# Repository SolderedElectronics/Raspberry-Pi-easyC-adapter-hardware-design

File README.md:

# Raspberry Pi easyC adapter Hardware design

## About the product

|  |
| :----------------------------------------------------------: |
|      [Buy Raspberry Pi easyC adapter](https://www.solde.red/333019)      |
This adapter makes it easy to connect easyC devices and sensors to the Raspberry Pi. It has 2 pieces of easyC connectors and a female header for Raspberry Pi, next to the header there are pins for connecting 5V and 3.3V and ground pins. It simply connects to the Raspberry Pi because its pinout matches the pinout of the Raspberry Pi. You can find more about easyC here.

## Repository contents

All Soldered Electronics hardware designed in KiCAD, and repositories are organized in the following way:

- CAD folder - contains KiCAD files (Schematics, Board, Panel Board), sorted by version. Change log lists all changes between versions.
- OUTPUTS - contains useful files, such as Bill of Materials (BOM), PDF of schematics, 3D .step file of the board and gerber files, sorted by version. 
- OUTPUTS -> Compliance - Certificates and useful legal stuff. 

## Want to contribute?

Please feel free to submit a pull request if you have any contributions. We encourage you to submit an issue or pull request if you find a bug. 

## About Soldered

At Soldered, we design and manufacture a wide selection of electronic products to help you turn your ideas into acts and bring you one step closer to your final project. Our products are intented for makers and crafted in-house by our experienced team in Osijek, Croatia. We believe that sharing is a crucial element for improvement and innovation, and we work hard to stay connected with all our makers regardless of their skill or experience level. Therefore, all our products are open-source. Finally, we always have your back. If you face any problem concerning either your shopping experience or your electronics project, our team will help you deal with it, offering efficient customer service and cost-free technical support anytime. Some of those might be useful for you:

- [Web Store](https://www.soldered.com/shop)
- [Tutorials & Projects](https://soldered.com/learn)
- [Community & Technical support](https://soldered.com/community)

## License info

All Soldered open-source hardware (OSH) is under The TAPR Open Hardware License. Read more in the LICENSE file. 

No warranty - all designs in this repository are distributed in the hope that they will be useful, but without any warranty. They are provided "AS IS", therefore without warranty of any kind, either expressed or implied. The entire quality and performance of what you do with the contents of this repository are your responsibility. In no event, Soldered Electronics will be liable for your damages, losses, including any general, special, incidental or consequential damage arising out of the use or inability to use the contents of this repository. 

## Have fun! 
And thank you from your fellow makers at Soldered Electronics.

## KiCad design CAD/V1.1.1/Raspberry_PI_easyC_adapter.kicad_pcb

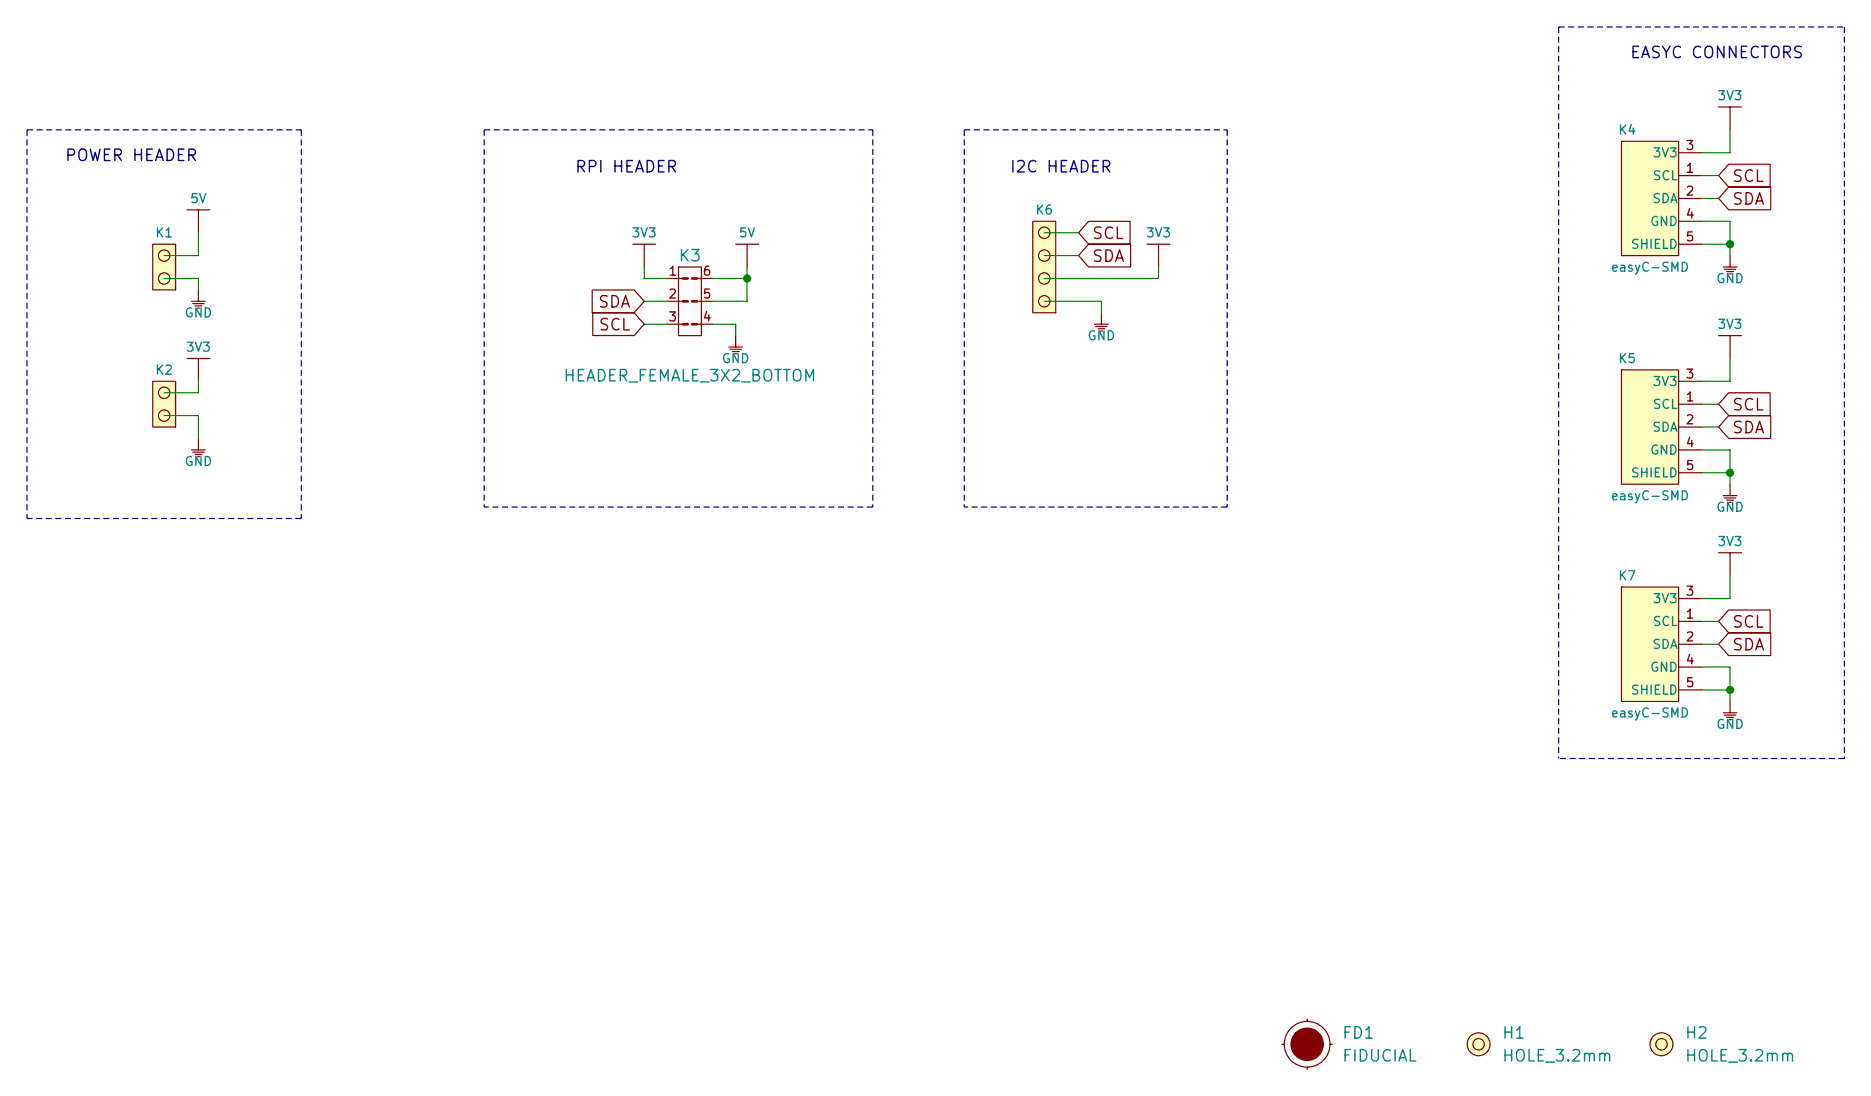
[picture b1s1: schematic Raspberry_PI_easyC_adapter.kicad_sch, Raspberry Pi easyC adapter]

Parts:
FD1: FIDUCIAL; FIDUCIAL_23
H1, H2: HOLE_3.2mm
K1, K2: HEADER_MALE_2X1
K3: HEADER_FEMALE_3X2_BOTTOM
K4, K5, K7: easyC-SMD; easyC-connector
K6: HEADER_MALE_4X1

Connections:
3V3: K2.2, K3.1, K4.3 (3V3), K5.3 (3V3), K6.2, K7.3 (3V3)
5V: K1.2, K3.5, K3.6
GND: K1.1, K2.1, K3.4, K4.4 (GND), K4.5 (SHIELD), K5.4 (GND), K5.5 (SHIELD), K6.1, K7.4 (GND), K7.5 (SHIELD)
SCL: K3.3, K4.1 (SCL), K5.1 (SCL), K6.4, K7.1 (SCL)
SDA: K3.2, K4.2 (SDA), K5.2 (SDA), K6.3, K7.2 (SDA)

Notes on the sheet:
POWER HEADER
RPI HEADER
I2C HEADER
EASYC CONNECTORS

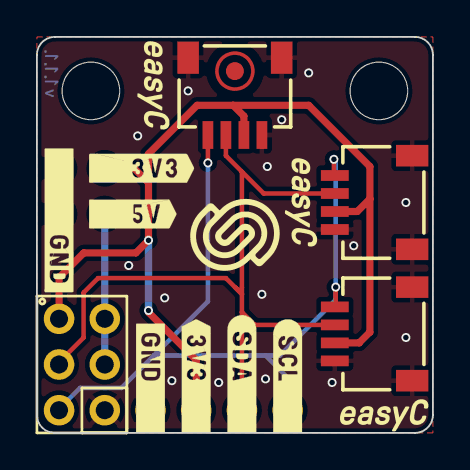
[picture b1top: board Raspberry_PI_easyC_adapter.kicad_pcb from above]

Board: 2 copper layers, 22.0 x 22.0 mm, 10 parts (0 on the bottom side), 5 nets.

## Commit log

2022-08-06 Updating open source files.
